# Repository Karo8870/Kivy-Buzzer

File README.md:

# Kivy Buzzer

This is a buzzer that I decided to name kivy because I think kiwi's make weird sounds and I will play with it with my friends

# Slack User
Project made by: cazacuchristian
aka. Karo

Materials:
 - PCB
 - Resistor
 - Button
 - Battery holder (+ battery if you want it to work)
 - Buzzer

## Schematic

## PCB

# 3D view

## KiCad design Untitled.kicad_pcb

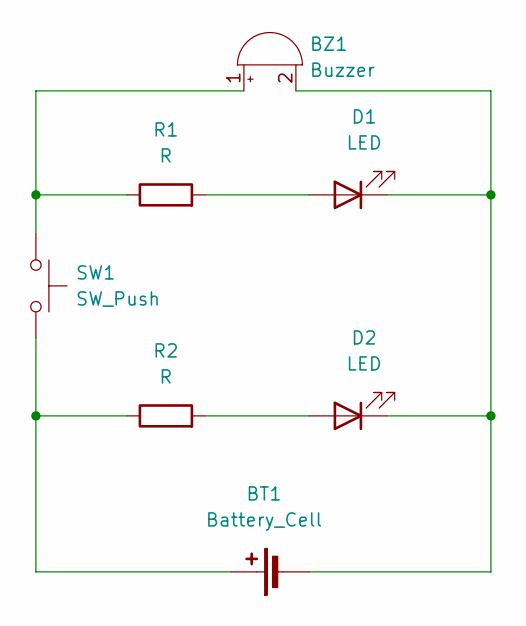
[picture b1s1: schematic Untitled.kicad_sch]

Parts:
BT1: Battery_Cell; BatteryHolder_Keystone_3034_1x20mm
BZ1: Buzzer; Buzzer_12x9.5RM7.6
D1, D2: LED; LED_D5.0mm
R1, R2: R; R_Axial_DIN0207_L6.3mm_D2.5mm_P7.62mm_Horizontal
SW1: SW_Push; SW_PUSH_6mm

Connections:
unnamed: BT1.1 (+), R2.1, SW1.2
unnamed: BT1.2 (-), BZ1.2 (-), D1.1 (K), D2.1 (K)
unnamed: BZ1.1 (+), R1.1, SW1.1
unnamed: D1.2 (A), R1.2
unnamed: D2.2 (A), R2.2

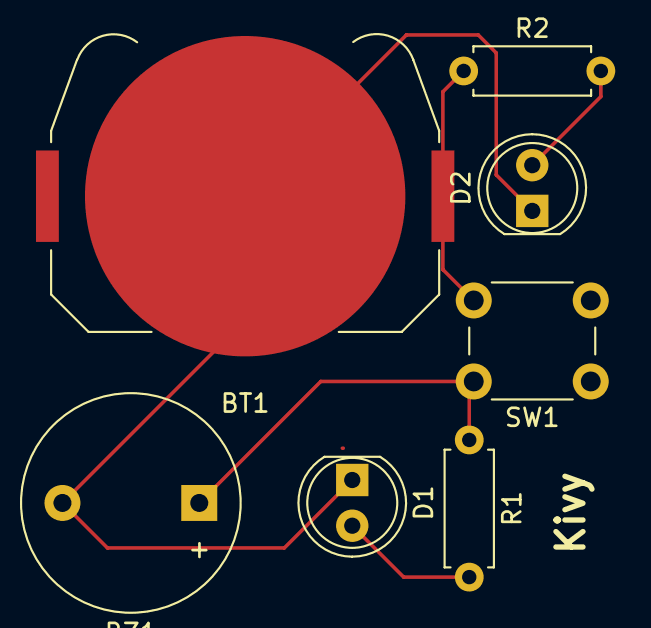
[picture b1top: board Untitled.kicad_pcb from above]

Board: 2 copper layers, 7 parts (0 on the bottom side), 5 nets.

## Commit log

2025-04-24 Added initial shematics and pcbs
2025-04-24 Added logo to schematic
2025-04-24 Added images and modified readme
2025-04-24 Added LEDs
